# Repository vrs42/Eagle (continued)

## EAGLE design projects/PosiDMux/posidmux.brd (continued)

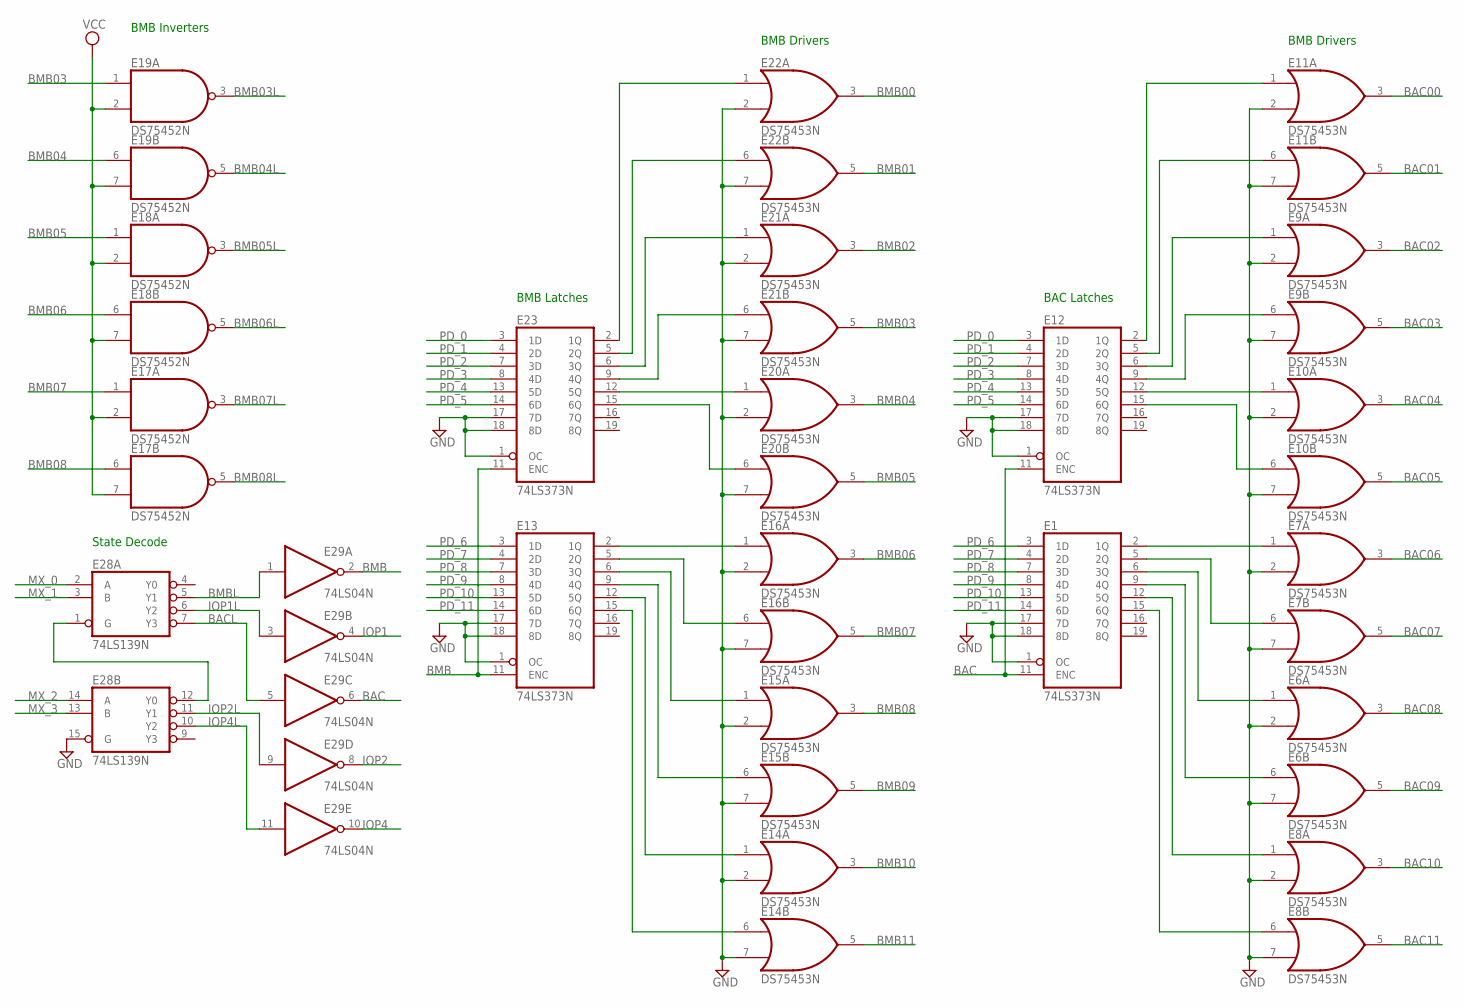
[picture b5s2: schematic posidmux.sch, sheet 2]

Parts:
E1, E12, E13, E23: 74LS373N; DIL20
E6, E7, E8, E9, E10, E11, E14, E15, E16, E20, E21, E22: DS75453N; DIL08
E17, E18, E19: DS75452N; DIL08
E28: 74LS139N; DIL16
E29: 74LS04N; DIL14

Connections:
BAC: E1.11 (ENC), E12.11 (ENC), E29.6 (O)
BAC00: E11.3 (O); also elsewhere on the board
BAC01: E11.5 (O); also elsewhere on the board
BAC02: E9.3 (O); also elsewhere on the board
BAC03: E9.5 (O); also elsewhere on the board
BAC04: E10.3 (O); also elsewhere on the board
BAC05: E10.5 (O); also elsewhere on the board
BAC06: E7.3 (O); also elsewhere on the board
BAC07: E7.5 (O); also elsewhere on the board
BAC08: E6.3 (O); also elsewhere on the board
BAC09: E6.5 (O); also elsewhere on the board
BAC10: E8.3 (O); also elsewhere on the board
BAC11: E8.5 (O); also elsewhere on the board
BACL: E28.7 (Y3), E29.5 (I)
BMB: E13.11 (ENC), E23.11 (ENC), E29.2 (O)
BMB00: E22.3 (O); also elsewhere on the board
BMB01: E22.5 (O); also elsewhere on the board
BMB02: E21.3 (O); also elsewhere on the board
BMB03: E19.1 (I0), E21.5 (O); also elsewhere on the board
BMB03L: E19.3 (O); also elsewhere on the board
BMB04: E19.6 (I0), E20.3 (O); also elsewhere on the board
BMB04L: E19.5 (O); also elsewhere on the board
BMB05: E18.1 (I0), E20.5 (O); also elsewhere on the board
BMB05L: E18.3 (O); also elsewhere on the board
BMB06: E16.3 (O), E18.6 (I0); also elsewhere on the board
BMB06L: E18.5 (O); also elsewhere on the board
BMB07: E16.5 (O), E17.1 (I0); also elsewhere on the board
BMB07L: E17.3 (O); also elsewhere on the board
BMB08: E15.3 (O), E17.6 (I0); also elsewhere on the board
BMB08L: E17.5 (O); also elsewhere on the board
BMB09: E15.5 (O); also elsewhere on the board
BMB10: E14.3 (O); also elsewhere on the board
BMB11: E14.5 (O); also elsewhere on the board
BMBL: E28.5 (Y1), E29.1 (I)
GND: E1.1 (OC), E1.10 (GND), E1.17 (7D), E1.18 (8D), E6.2 (I1), E6.4 (GND), E6.7 (I1), E7.2 (I1), E7.4 (GND), E7.7 (I1), E8.2 (I1), E8.4 (GND), E8.7 (I1), E9.2 (I1), E9.4 (GND), E9.7 (I1), E10.2 (I1), E10.4 (GND), E10.7 (I1), E11.2 (I1), E11.4 (GND), E11.7 (I1), E12.1 (OC), E12.10 (GND), E12.17 (7D), E12.18 (8D), E13.1 (OC), E13.10 (GND), E13.17 (7D), E13.18 (8D), E14.2 (I1), E14.4 (GND), E14.7 (I1), E15.2 (I1), E15.4 (GND), E15.7 (I1), E16.2 (I1), E16.4 (GND), E16.7 (I1), E17.4 (GND), E18.4 (GND), E19.4 (GND), E20.2 (I1), E20.4 (GND), E20.7 (I1), E21.2 (I1), E21.4 (GND), E21.7 (I1), E22.2 (I1), E22.4 (GND), E22.7 (I1), E23.1 (OC), E23.10 (GND), E23.17 (7D), E23.18 (8D), E28.8 (GND), E28.15 (G), E29.7 (GND); also elsewhere on the board
IOP1: E29.4 (O); also elsewhere on the board
IOP1L: E28.6 (Y2), E29.3 (I); also elsewhere on the board
IOP2: E29.8 (O); also elsewhere on the board
IOP2L: E28.11 (Y1), E29.9 (I); also elsewhere on the board
IOP4: E29.10 (O); also elsewhere on the board
IOP4L: E28.10 (Y2), E29.11 (I); also elsewhere on the board
MX_0: E28.2 (A); also elsewhere on the board
MX_00XX: E28.1 (G), E28.12 (Y0)
MX_1: E28.3 (B); also elsewhere on the board
MX_2: E28.14 (A); also elsewhere on the board
MX_3: E28.13 (B); also elsewhere on the board
unnamed: E22.1 (I0), E23.2 (1Q)
unnamed: E22.6 (I0), E23.5 (2Q)
unnamed: E21.1 (I0), E23.6 (3Q)
unnamed: E21.6 (I0), E23.9 (4Q)
unnamed: E20.1 (I0), E23.12 (5Q)
unnamed: E13.15 (6Q), E14.6 (I0)
unnamed: E13.12 (5Q), E14.1 (I0)
unnamed: E13.9 (4Q), E15.6 (I0)
unnamed: E13.6 (3Q), E15.1 (I0)
unnamed: E13.5 (2Q), E16.6 (I0)
unnamed: E13.2 (1Q), E16.1 (I0)
unnamed: E20.6 (I0), E23.15 (6Q)
unnamed: E11.1 (I0), E12.2 (1Q)
unnamed: E11.6 (I0), E12.5 (2Q)
unnamed: E9.1 (I0), E12.6 (3Q)
unnamed: E9.6 (I0), E12.9 (4Q)
unnamed: E10.1 (I0), E12.12 (5Q)
unnamed: E1.15 (6Q), E8.6 (I0)
unnamed: E1.12 (5Q), E8.1 (I0)
unnamed: E1.9 (4Q), E6.6 (I0)
unnamed: E1.6 (3Q), E6.1 (I0)
unnamed: E1.5 (2Q), E7.6 (I0)
unnamed: E10.6 (I0), E12.15 (6Q)
unnamed: E1.2 (1Q), E7.1 (I0)
PD_0: E12.3 (1D), E23.3 (1D); also elsewhere on the board
PD_1: E12.4 (2D), E23.4 (2D); also elsewhere on the board
PD_2: E12.7 (3D), E23.7 (3D); also elsewhere on the board
PD_3: E12.8 (4D), E23.8 (4D); also elsewhere on the board
PD_4: E12.13 (5D), E23.13 (5D); also elsewhere on the board
PD_5: E12.14 (6D), E23.14 (6D); also elsewhere on the board
PD_6: E1.3 (1D), E13.3 (1D); also elsewhere on the board
PD_7: E1.4 (2D), E13.4 (2D); also elsewhere on the board
PD_8: E1.7 (3D), E13.7 (3D); also elsewhere on the board
PD_9: E1.8 (4D), E13.8 (4D); also elsewhere on the board
PD_10: E1.13 (5D), E13.13 (5D); also elsewhere on the board
PD_11: E1.14 (6D), E13.14 (6D); also elsewhere on the board
VCC: E1.20 (VCC), E6.8 (VCC), E7.8 (VCC), E8.8 (VCC), E9.8 (VCC), E10.8 (VCC), E11.8 (VCC), E12.20 (VCC), E13.20 (VCC), E14.8 (VCC), E15.8 (VCC), E16.8 (VCC), E17.2 (I1), E17.7 (I1), E17.8 (VCC), E18.2 (I1), E18.7 (I1), E18.8 (VCC), E19.2 (I1), E19.7 (I1), E19.8 (VCC), E20.8 (VCC), E21.8 (VCC), E22.8 (VCC), E23.20 (VCC), E28.16 (VCC), E29.14 (VCC); also elsewhere on the board

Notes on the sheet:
State Decode
BMB Latches
BMB Drivers
BMB Inverters
BAC Latches

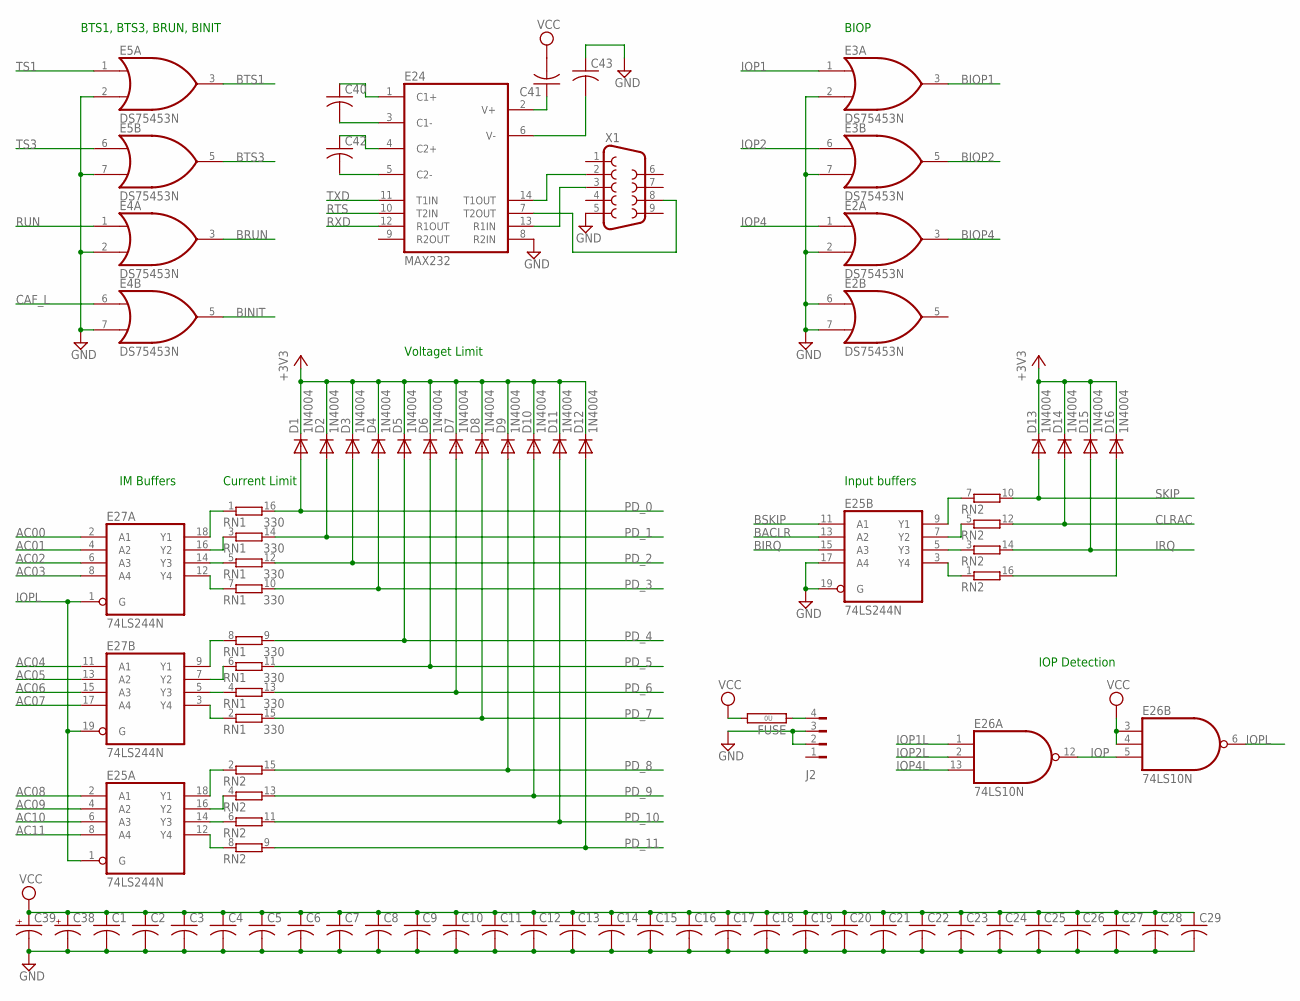
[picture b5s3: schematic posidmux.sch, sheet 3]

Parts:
C1, C2, C3, C4, C5, C6, C7, C8, C9, C10, C11, C12, C13, C14, C15, C16, C17, C18, C19, C20, C21, C22, C23, C24, C25, C26, C27, C28, C29, C40, C41, C42, C43: C-US050-025X075; C050-025X075
C38, C39: CPOL-USE22-6AXIAL; E22-6
D1, D2, D3, D4, D5, D6, D7, D8, D9, D10, D11, D12, D13, D14, D15, D16: 1N4004; DO41-10
E2, E3, E4, E5: DS75453N; DIL08
E24: MAX232; DIL16
E25, E27: 74LS244N; DIL20
E26: 74LS10N; DIL14
FUSE: 0R; 0R/10
J2: FLOPPY-4
RN1: 330; DIL16
RN2: 8R-P; DIL16
X1: F09HP

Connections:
+3V3: D1.C, D2.C, D3.C, D4.C, D5.C, D6.C, D7.C, D8.C, D9.C, D10.C, D11.C, D12.C, D13.C, D14.C, D15.C, D16.C; also elsewhere on the board
AC00: E27.2 (A1); also elsewhere on the board
AC01: E27.4 (A2); also elsewhere on the board
AC02: E27.6 (A3); also elsewhere on the board
AC03: E27.8 (A4); also elsewhere on the board
AC04: E27.11 (A1); also elsewhere on the board
AC05: E27.13 (A2); also elsewhere on the board
AC06: E27.15 (A3); also elsewhere on the board
AC07: E27.17 (A4); also elsewhere on the board
AC08: E25.2 (A1); also elsewhere on the board
AC09: E25.4 (A2); also elsewhere on the board
AC10: E25.6 (A3); also elsewhere on the board
AC11: E25.8 (A4); also elsewhere on the board
BACLR: E25.13 (A2); also elsewhere on the board
BINIT: E4.5 (O); also elsewhere on the board
BIOP1: E3.3 (O); also elsewhere on the board
BIOP2: E3.5 (O); also elsewhere on the board
BIOP4: E2.3 (O); also elsewhere on the board
BIRQ: E25.15 (A3); also elsewhere on the board
BRUN: E4.3 (O); also elsewhere on the board
BSKIP: E25.11 (A1); also elsewhere on the board
BTS1: E5.3 (O); also elsewhere on the board
BTS3: E5.5 (O); also elsewhere on the board
CAF_L: E4.6 (I0); also elsewhere on the board
CLRAC: D14.A, RN2.12 (2); also elsewhere on the board
GND: C1.2, C2.2, C3.2, C4.2, C5.2, C6.2, C7.2, C8.2, C9.2, C10.2, C11.2, C12.2, C13.2, C14.2, C15.2, C16.2, C17.2, C18.2, C19.2, C20.2, C21.2, C22.2, C23.2, C24.2, C25.2, C26.2, C27.2, C28.2, C29.2, C38.-, C39.-, C43.1, E2.2 (I1), E2.4 (GND), E2.6 (I0), E2.7 (I1), E3.2 (I1), E3.4 (GND), E3.7 (I1), E4.2 (I1), E4.4 (GND), E4.7 (I1), E5.2 (I1), E5.4 (GND), E5.7 (I1), E24.8 (R2IN), E24.15 (GND), E25.10 (GND), E25.17 (A4), E25.19 (G), E26.7 (GND), E27.10 (GND), J2.2, J2.3, X1.5; also elsewhere on the board
IOP: E26.5 (I2), E26.12 (O)
IOP1: E3.1 (I0); also elsewhere on the board
IOP1L: E26.1 (I0); also elsewhere on the board
IOP2: E3.6 (I0); also elsewhere on the board
IOP2L: E26.2 (I1); also elsewhere on the board
IOP4: E2.1 (I0); also elsewhere on the board
IOP4L: E26.13 (I2); also elsewhere on the board
IOPL: E25.1 (G), E26.6 (O), E27.1 (G), E27.19 (G)
IRQ: D15.A, RN2.14 (2); also elsewhere on the board
unnamed: E27.18 (Y1), RN1.1
unnamed: E27.16 (Y2), RN1.3 (1)
unnamed: E27.14 (Y3), RN1.5 (1)
unnamed: E27.12 (Y4), RN1.7 (1)
unnamed: E27.9 (Y1), RN1.8 (1)
unnamed: E27.7 (Y2), RN1.6 (1)
unnamed: E27.5 (Y3), RN1.4 (1)
unnamed: E27.3 (Y4), RN1.2 (1)
unnamed: E25.16 (Y2), RN2.4 (1)
unnamed: E25.18 (Y1), RN2.2 (1)
unnamed: E25.14 (Y3), RN2.6 (1)
unnamed: E25.12 (Y4), RN2.8 (1)
unnamed: E25.9 (Y1), RN2.7 (1)
unnamed: E25.7 (Y2), RN2.5 (1)
unnamed: E25.5 (Y3), RN2.3 (1)
unnamed: E25.3 (Y4), RN2.1
unnamed: FUSE.1, J2.4
unnamed: D16.A, RN2.16 (2)
unnamed: E24.14 (T1OUT), X1.2
unnamed: E24.7 (T2OUT), X1.8
unnamed: E24.13 (R1IN), X1.3
unnamed: C42.2, E24.5 (C2-)
unnamed: C42.1, E24.4 (C2+)
unnamed: C40.2, E24.3 (C1-)
unnamed: C40.1, E24.1 (C1+)
unnamed: C41.1, E24.2 (V+)
unnamed: C43.2, E24.6 (V-)
PD_0: D1.A, RN1.16 (2); also elsewhere on the board
PD_1: D2.A, RN1.14 (2); also elsewhere on the board
PD_2: D3.A, RN1.12 (2); also elsewhere on the board
PD_3: D4.A, RN1.10 (2); also elsewhere on the board
PD_4: D5.A, RN1.9 (2); also elsewhere on the board
PD_5: D6.A, RN1.11 (2); also elsewhere on the board
PD_6: D7.A, RN1.13 (2); also elsewhere on the board
PD_7: D8.A, RN1.15 (2); also elsewhere on the board
PD_8: D9.A, RN2.15 (2); also elsewhere on the board
PD_9: D10.A, RN2.13 (2); also elsewhere on the board
PD_10: D11.A, RN2.11 (2); also elsewhere on the board
PD_11: D12.A, RN2.9 (2); also elsewhere on the board
RTS: E24.10 (T2IN); also elsewhere on the board
RUN: E4.1 (I0); also elsewhere on the board
RXD: E24.12 (R1OUT); also elsewhere on the board
SKIP: D13.A, RN2.10 (2); also elsewhere on the board
TS1: E5.1 (I0); also elsewhere on the board
TS3: E5.6 (I0); also elsewhere on the board
TXD: E24.11 (T1IN); also elsewhere on the board
VCC: C1.1, C2.1, C3.1, C4.1, C5.1, C6.1, C7.1, C8.1, C9.1, C10.1, C11.1, C12.1, C13.1, C14.1, C15.1, C16.1, C17.1, C18.1, C19.1, C20.1, C21.1, C22.1, C23.1, C24.1, C25.1, C26.1, C27.1, C28.1, C29.1, C38.+, C39.+, C41.2, E2.8 (VCC), E3.8 (VCC), E4.8 (VCC), E5.8 (VCC), E24.16 (VCC), E25.20 (VCC), E26.3 (I0), E26.4 (I1), E26.14 (VCC), E27.20 (VCC), FUSE.2; also elsewhere on the board

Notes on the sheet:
Input buffers
IM Buffers
BTS1, BTS3, BRUN, BINIT
Current Limit
Voltaget Limit
BIOP
IOP Detection

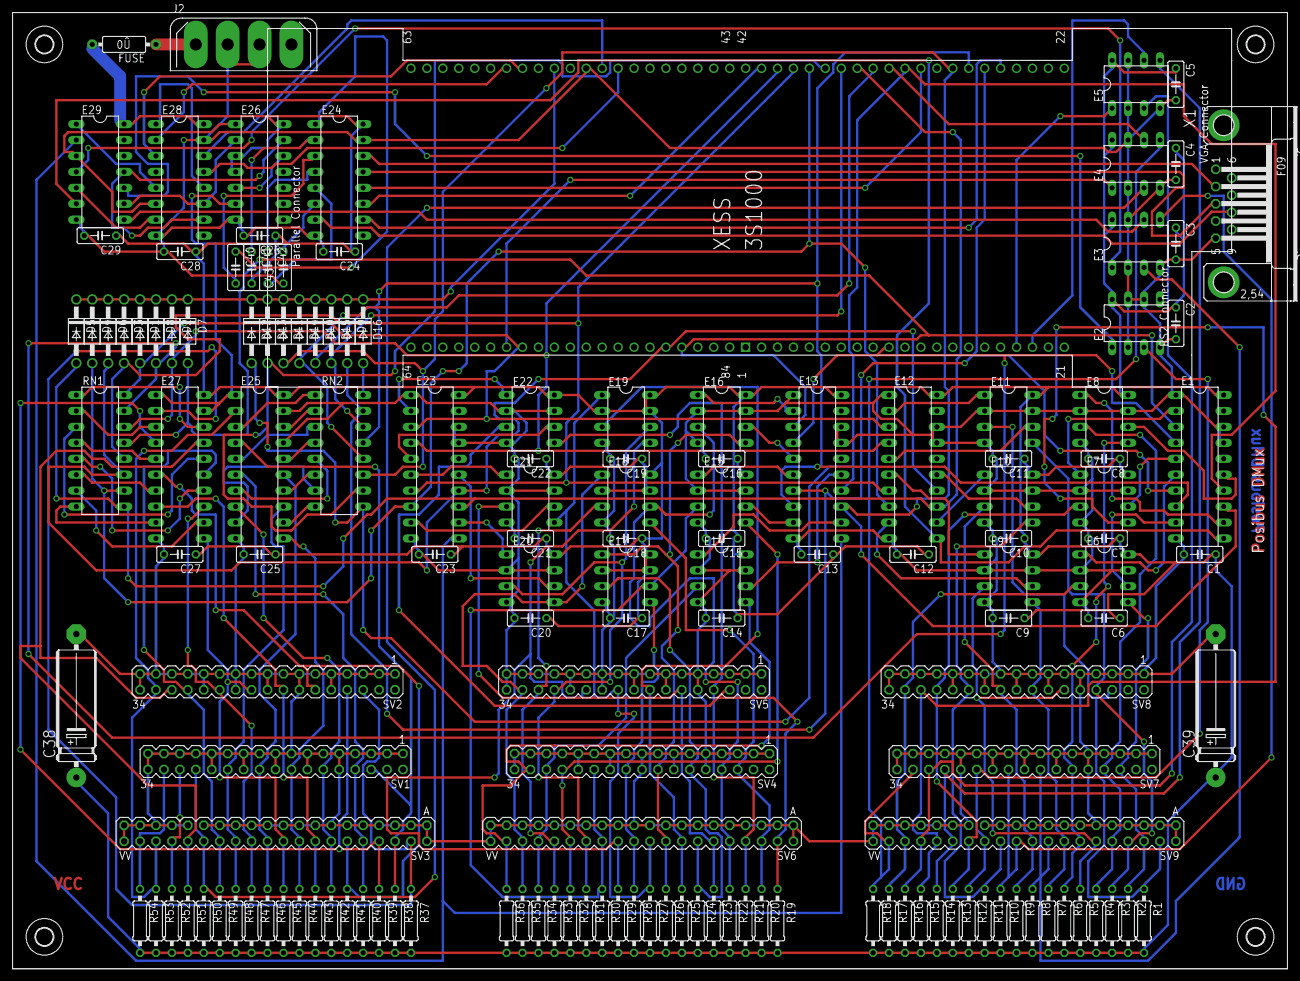
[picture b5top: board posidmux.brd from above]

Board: 2 copper layers, 203.2 x 152.4 mm, 153 parts (0 on the bottom side), 147 nets.

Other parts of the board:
U$1, U$2, U$3, U$4: 2,8

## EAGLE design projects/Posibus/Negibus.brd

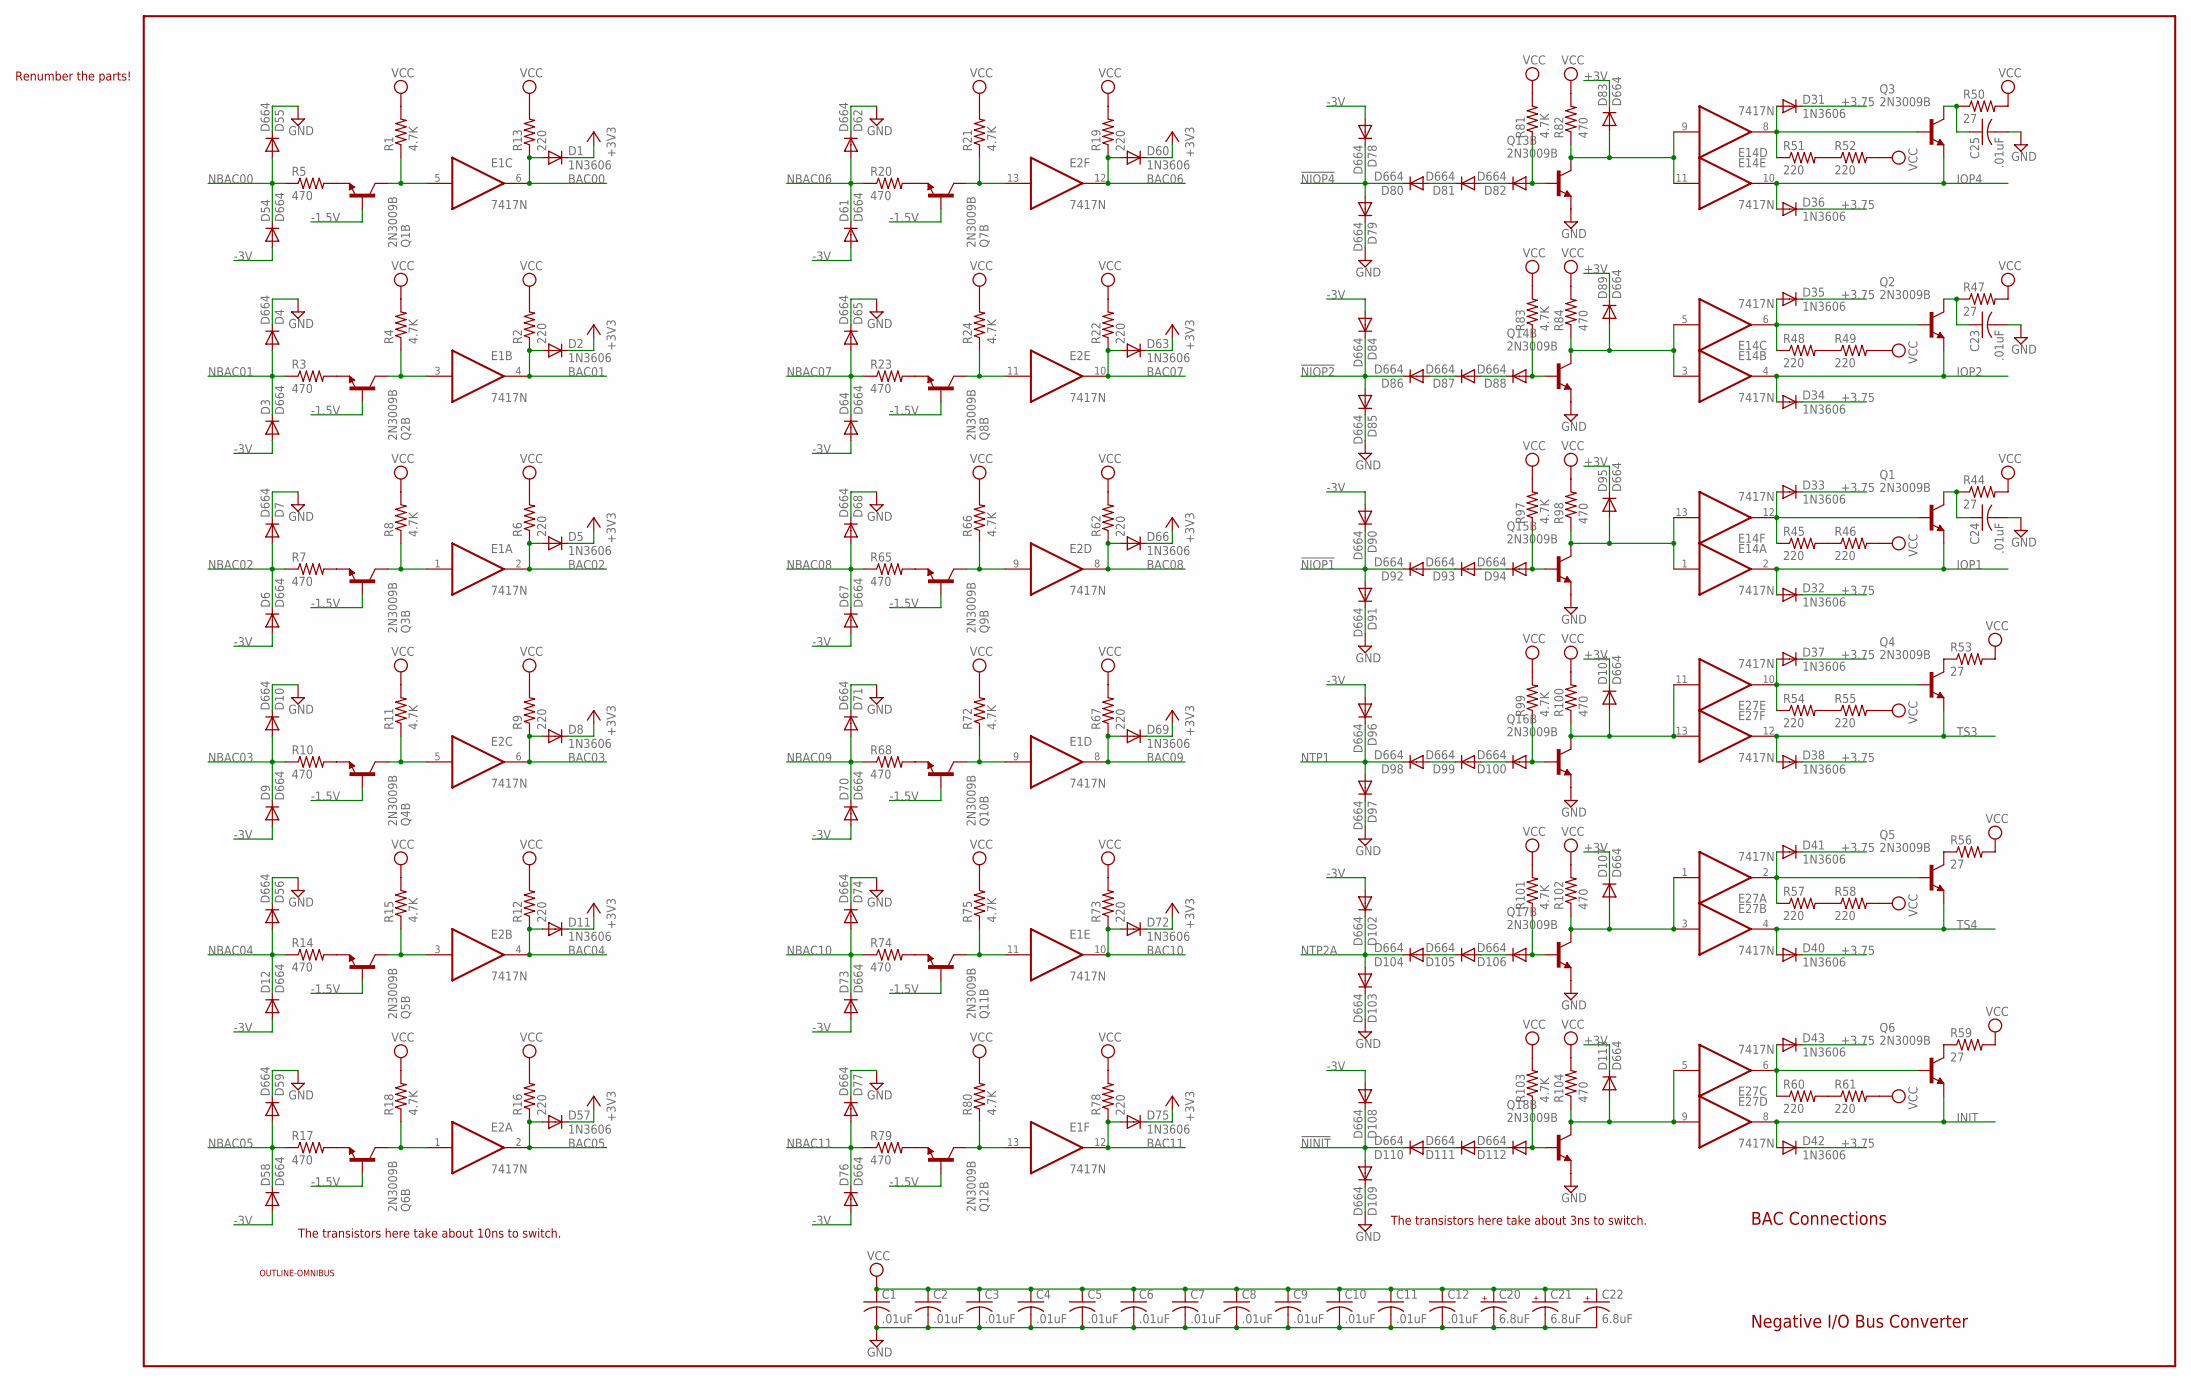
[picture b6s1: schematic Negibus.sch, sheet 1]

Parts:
C1, C2, C3, C4, C5, C6, C7, C8, C9, C10, C11, C12, C23, C24, C25: .01uF; C050-025X075
C20, C21, C22: 6.8uF; E12-8
D1, D2, D5, D8, D11, D31, D32, D33, D34, D35, D36, D37, D38, D40, D41, D42, D43, D57, D60, D63, D66, D69, D72, D75: 1N3606; DO35-10
D3, D4, D6, D7, D9, D10, D12, D54, D55, D56, D58, D59, D61, D62, D64, D65, D67, D68, D70, D71, D73, D74, D76, D77, D78, D79, D80, D81, D82, D83, D84, D85, D86, D87, D88, D89, D90, D91, D92, D93, D94, D95, D96, D97, D98, D99, D100, D101, D102, D103, D104, D105, D106, D107, D108, D109, D110, D111, D112, D113: D664; DO35-10
E1, E2, E14, E27: 7417N; DIL14
Q1, Q2, Q3, Q4, Q5, Q6: 2N3009B; TO5
Q1B, Q2B, Q3B, Q4B, Q5B, Q6B, Q7B, Q8B, Q9B, Q10B, Q11B, Q12B, Q13B, Q14B, Q15B, Q16B, Q17B, Q18B: 2N3009B; TO39
R1, R4, R8, R11, R15, R18, R21, R24, R66, R72, R75, R80, R81, R83, R97, R99, R101, R103: 4.7K; 0207/10
R2, R6, R9, R12, R13, R16, R19, R22, R45, R46, R48, R49, R51, R52, R54, R55, R57, R58, R60, R61, R62, R67, R73, R78: 220; 0207/10
R3, R5, R7, R10, R14, R17, R20, R23, R65, R68, R74, R79, R82, R84, R98, R100, R102, R104: 470; 0207/10
R44, R47, R50, R53, R56, R59: 27; 0411/12
U$1: OUTLINE-OMNIBUS; OMNIBUS

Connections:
!NINIT: D108.C, D109.A, D110.C; also elsewhere on the board
!NIOP1: D90.C, D91.A, D92.C; also elsewhere on the board
!NIOP2: D84.C, D85.A, D86.C; also elsewhere on the board
!NIOP4: D78.C, D79.A, D80.C; also elsewhere on the board
+3.75: D31.C, D32.C, D33.C, D34.C, D35.C, D36.C, D37.C, D38.C, D40.C, D41.C, D42.C, D43.C; also elsewhere on the board
+3V: D83.C, D89.C, D95.C, D101.C, D107.C, D113.C
+3V3: D1.C, D2.C, D5.C, D8.C, D11.C, D57.C, D60.C, D63.C, D66.C, D69.C, D72.C, D75.C; also elsewhere on the board
-1.5V: Q1B.2 (B), Q2B.2 (B), Q3B.2 (B), Q4B.2 (B), Q5B.2 (B), Q6B.2 (B), Q7B.2 (B), Q8B.2 (B), Q9B.2 (B), Q10B.2 (B), Q11B.2 (B), Q12B.2 (B); also elsewhere on the board
-3V: D3.A, D6.A, D9.A, D12.A, D54.A, D58.A, D61.A, D64.A, D67.A, D70.A, D73.A, D76.A, D78.A, D84.A, D90.A, D96.A, D102.A, D108.A; also elsewhere on the board
BAC00: D1.A, E1.6 (O), R13.1; also elsewhere on the board
BAC01: D2.A, E1.4 (O), R2.1; also elsewhere on the board
BAC02: D5.A, E1.2 (O), R6.1; also elsewhere on the board
BAC03: D8.A, E2.6 (O), R9.1; also elsewhere on the board
BAC04: D11.A, E2.4 (O), R12.1; also elsewhere on the board
BAC05: D57.A, E2.2 (O), R16.1; also elsewhere on the board
BAC06: D60.A, E2.12 (O), R19.1; also elsewhere on the board
BAC07: D63.A, E2.10 (O), R22.1; also elsewhere on the board
BAC08: D66.A, E2.8 (O), R62.1; also elsewhere on the board
BAC09: D69.A, E1.8 (O), R67.1; also elsewhere on the board
BAC10: D72.A, E1.10 (O), R73.1; also elsewhere on the board
BAC11: D75.A, E1.12 (O), R78.1; also elsewhere on the board
GND: C1.2, C2.2, C3.2, C4.2, C5.2, C6.2, C7.2, C8.2, C9.2, C10.2, C11.2, C12.2, C20.-, C21.-, C22.-, C23.2, C24.2, C25.2, D4.C, D7.C, D10.C, D55.C, D56.C, D59.C, D62.C, D65.C, D68.C, D71.C, D74.C, D77.C, D79.C, D85.C, D91.C, D97.C, D103.C, D109.C, E1.7 (GND), E2.7 (GND), E14.7 (GND), E27.7 (GND), Q13B.1 (E), Q14B.1 (E), Q15B.1 (E), Q16B.1 (E), Q17B.1 (E), Q18B.1 (E); also elsewhere on the board
INIT: D42.A, E27.8 (O), Q6.1 (E); also elsewhere on the board
IOP1: D32.A, E14.2 (O), Q1.1 (E); also elsewhere on the board
IOP2: D34.A, E14.4 (O), Q2.1 (E); also elsewhere on the board
IOP4: D36.A, E14.10 (O), Q3.1 (E); also elsewhere on the board
unnamed: Q2B.1 (E), R3.2
unnamed: D89.A, E14.3 (I), E14.5 (I), Q14B.3 (C), R84.1
unnamed: Q1B.1 (E), R5.2
unnamed: E1.5 (I), Q1B.3 (C), R1.1
unnamed: E1.3 (I), Q2B.3 (C), R4.1
unnamed: Q3B.1 (E), R7.2
unnamed: E1.1 (I), Q3B.3 (C), R8.1
unnamed: Q4B.1 (E), R10.2
unnamed: E2.5 (I), Q4B.3 (C), R11.1
unnamed: Q5B.1 (E), R14.2
unnamed: E2.3 (I), Q5B.3 (C), R15.1
unnamed: Q6B.1 (E), R17.2
unnamed: E2.1 (I), Q6B.3 (C), R18.1
unnamed: Q7B.1 (E), R20.2
unnamed: E2.13 (I), Q7B.3 (C), R21.1
unnamed: Q8B.1 (E), R23.2
unnamed: E2.11 (I), Q8B.3 (C), R24.1
unnamed: Q9B.1 (E), R65.2
unnamed: E2.9 (I), Q9B.3 (C), R66.1
unnamed: Q10B.1 (E), R68.2
unnamed: E1.9 (I), Q10B.3 (C), R72.1
unnamed: Q11B.1 (E), R74.2
unnamed: E1.11 (I), Q11B.3 (C), R75.1
unnamed: Q12B.1 (E), R79.2
unnamed: E1.13 (I), Q12B.3 (C), R80.1
unnamed: D82.A, Q13B.2 (B), R81.1
unnamed: D80.A, D81.C
unnamed: D88.A, Q14B.2 (B), R83.1
unnamed: D86.A, D87.C
unnamed: D87.A, D88.C
unnamed: D94.A, Q15B.2 (B), R97.1
unnamed: R54.2, R55.1
unnamed: D92.A, D93.C
unnamed: D101.A, E27.11 (I), E27.13 (I), Q16B.3 (C), R100.1
unnamed: D37.A, E27.10 (O), Q4.2 (B), R54.1
unnamed: Q4.3 (C), R53.1
unnamed: D93.A, D94.C
unnamed: D41.A, E27.2 (O), Q5.2 (B), R57.1
unnamed: D95.A, E14.1 (I), E14.13 (I), Q15B.3 (C), R98.1
unnamed: D107.A, E27.1 (I), E27.3 (I), Q17B.3 (C), R102.1
unnamed: R57.2, R58.1
unnamed: Q5.3 (C), R56.1
unnamed: D100.A, Q16B.2 (B), R99.1
unnamed: D98.A, D99.C
unnamed: D113.A, E27.5 (I), E27.9 (I), Q18B.3 (C), R104.1
unnamed: R60.2, R61.1
unnamed: D43.A, E27.6 (O), Q6.2 (B), R60.1
unnamed: Q6.3 (C), R59.1
unnamed: D99.A, D100.C
unnamed: D81.A, D82.C
unnamed: D83.A, E14.9 (I), E14.11 (I), Q13B.3 (C), R82.1
unnamed: D106.A, Q17B.2 (B), R101.1
unnamed: D104.A, D105.C
unnamed: D105.A, D106.C
unnamed: D112.A, Q18B.2 (B), R103.1
unnamed: D110.A, D111.C
unnamed: D111.A, D112.C
unnamed: D35.A, E14.6 (O), Q2.2 (B), R48.1
unnamed: D33.A, E14.12 (O), Q1.2 (B), R45.1
unnamed: R48.2, R49.1
unnamed: R51.2, R52.1
unnamed: D31.A, E14.8 (O), Q3.2 (B), R51.1
unnamed: C25.1, Q3.3 (C), R50.1
unnamed: C23.1, Q2.3 (C), R47.1
unnamed: C24.1, Q1.3 (C), R44.1
unnamed: R45.2, R46.1
NBAC00: D54.C, D55.A, R5.1; also elsewhere on the board
NBAC01: D3.C, D4.A, R3.1; also elsewhere on the board
NBAC02: D6.C, D7.A, R7.1; also elsewhere on the board
NBAC03: D9.C, D10.A, R10.1; also elsewhere on the board
NBAC04: D12.C, D56.A, R14.1; also elsewhere on the board
NBAC05: D58.C, D59.A, R17.1; also elsewhere on the board
NBAC06: D61.C, D62.A, R20.1; also elsewhere on the board
NBAC07: D64.C, D65.A, R23.1; also elsewhere on the board
NBAC08: D67.C, D68.A, R65.1; also elsewhere on the board
NBAC09: D70.C, D71.A, R68.1; also elsewhere on the board
NBAC10: D73.C, D74.A, R74.1; also elsewhere on the board
NBAC11: D76.C, D77.A, R79.1; also elsewhere on the board
NTP1: D96.C, D97.A, D98.C; also elsewhere on the board
NTP2A: D102.C, D103.A, D104.C; also elsewhere on the board
TS3: D38.A, E27.12 (O), Q4.1 (E); also elsewhere on the board
TS4: D40.A, E27.4 (O), Q5.1 (E); also elsewhere on the board
VCC: C1.1, C2.1, C3.1, C4.1, C5.1, C6.1, C7.1, C8.1, C9.1, C10.1, C11.1, C12.1, C20.+, C21.+, C22.+, E1.14 (VCC), E2.14 (VCC), E14.14 (VCC), E27.14 (VCC), R1.2, R2.2, R4.2, R6.2, R8.2, R9.2, R11.2, R12.2, R13.2, R15.2, R16.2, R18.2, R19.2, R21.2, R22.2, R24.2, R44.2, R46.2, R47.2, R49.2, R50.2, R52.2, R53.2, R55.2, R56.2, R58.2, R59.2, R61.2, R62.2, R66.2, R67.2, R72.2, R73.2, R75.2, R78.2, R80.2, R81.2, R82.2, R83.2, R84.2, R97.2, R98.2, R99.2, R100.2, R101.2, R102.2, R103.2, R104.2; also elsewhere on the board

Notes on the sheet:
Negative I/O Bus Converter
BAC Connections
The transistors here take about 10ns to switch.
The transistors here take about 3ns to switch.
Renumber the parts!
